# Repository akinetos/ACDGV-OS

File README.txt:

Arduino - 1.8.15
ESP8266 Boards - 2.5.0

if (interface.anyProgramActive) {
    if (interface.showMenu) {
        if (> 2 seconds after activating or deactivating a program) {
            interface.showMenu = false;
        }
    }
}

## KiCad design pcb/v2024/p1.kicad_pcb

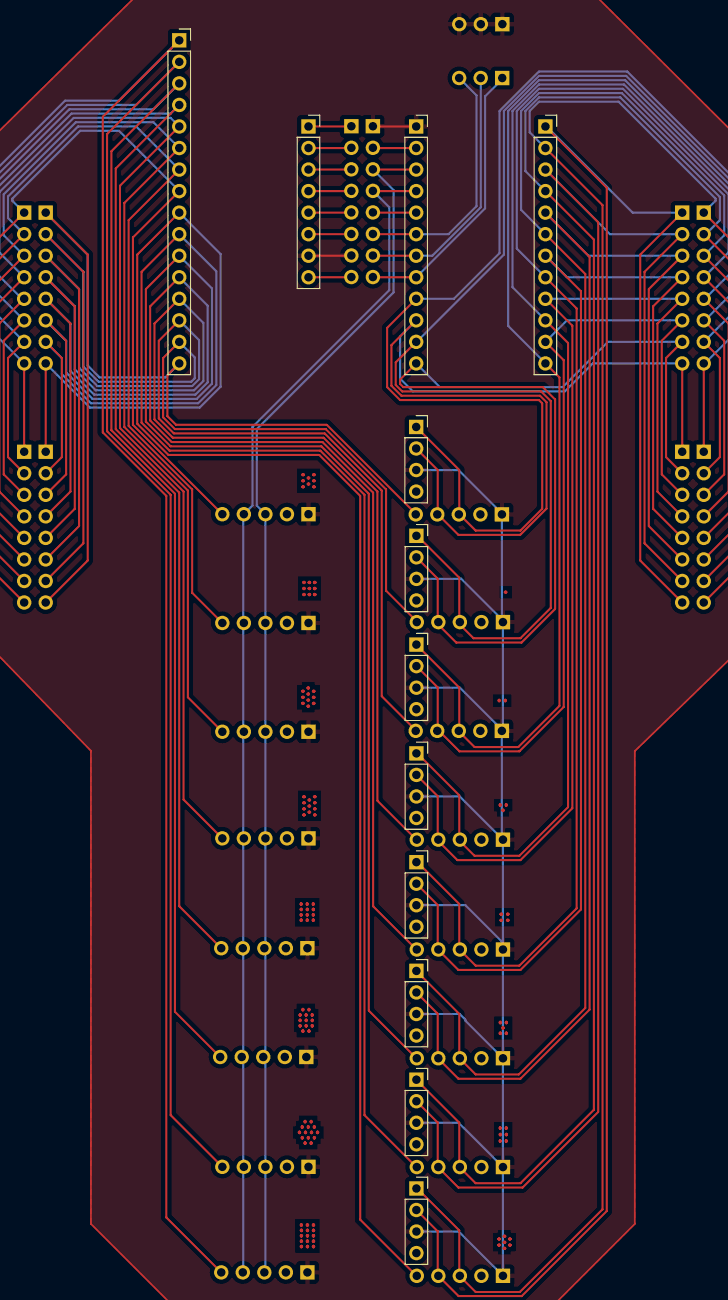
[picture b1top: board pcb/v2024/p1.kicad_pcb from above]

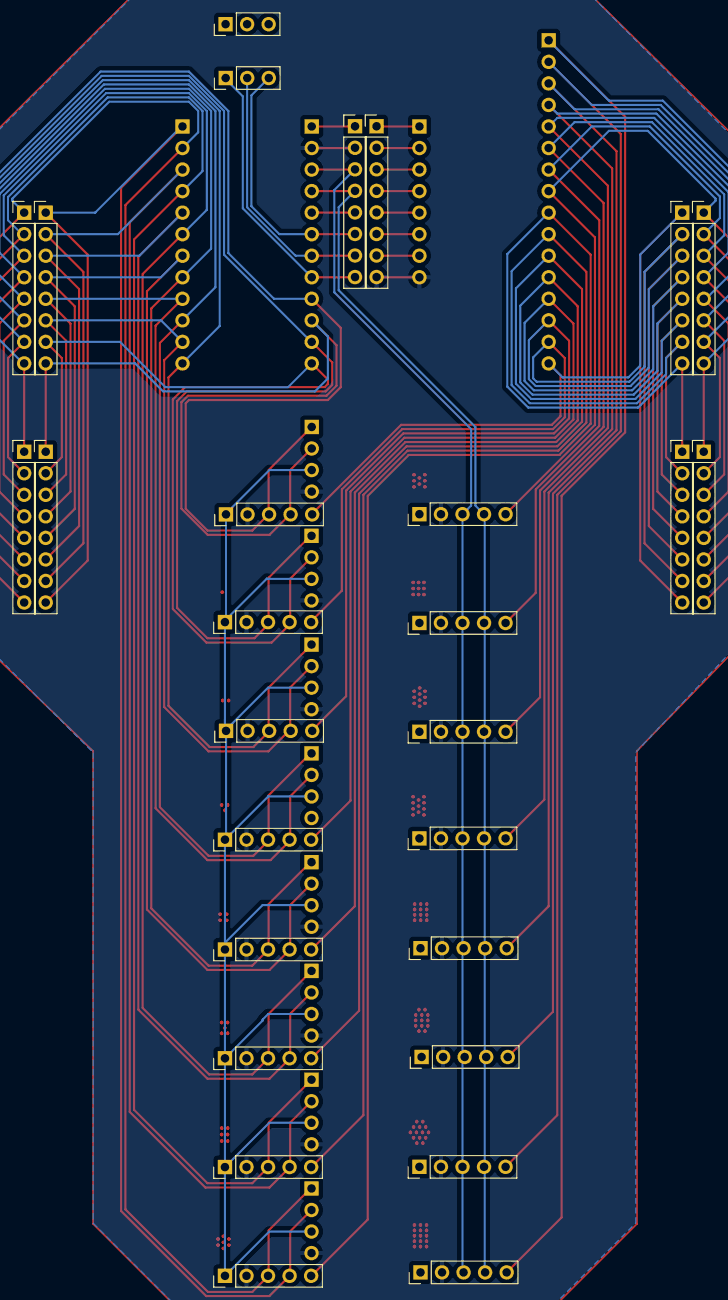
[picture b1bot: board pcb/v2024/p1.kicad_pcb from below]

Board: 2 copper layers, 40 parts (28 on the bottom side), 2 nets.

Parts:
3PIN1, 3PIN2: PinHeader_1x03_P2.54mm_Vertical
AnalogL1, AnalogL2, AnalogL3, AnalogL4: PinHeader_1x08_P2.54mm_Vertical
AnalogM1: PinSocket_1x08_P2.54mm_Vertical
AnalogM2: PinSocket_1x16_P2.54mm_Vertical
Glowne1, Glowne2: PinHeader_1x08_P2.54mm_Vertical
I2C1, I2C2, I2C3, I2C4: PinHeader_1x08_P2.54mm_Vertical
J8, J9, J10, J11, J12, J13, J14, J15: PinSocket_1x04_P2.54mm_Vertical
J16, J17, J18, J19, J20, J21, J22, J23, J24, J25, J26, J27, J28, J29, J30, J31: PinHeader_1x05_P2.54mm_Vertical
Multiplekser_I2C1, Multiplekser_I2C2: PinSocket_1x12_P2.54mm_Vertical

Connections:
GND: AnalogM1.8, Glowne1.8, Glowne2.2, J8.4, J9.4, J10.4, J12.4, J13.4, J14.4, J15.4, J16.4, J17.4, J18.4, J19.4, J20.4, J21.4, J22.4, J23.4, J24.4, J25.4, J26.4, J27.4, J28.4, J29.4, J30.4, J31.4, Multiplekser_I2C1.2
V: 3PIN1.1, 3PIN1.2, 3PIN1.3, AnalogM1.7, Glowne1.7, Glowne2.1, J8.3, J9.3, J10.3, J11.3, J12.3, J13.3, J14.3, J15.3, J16.5, J17.5, J18.5, J19.5, J20.5, J21.5, J22.5, J23.5, J24.5, J25.5, J26.5, J27.5, J28.5, J29.5, J30.5, J31.5, Multiplekser_I2C1.1

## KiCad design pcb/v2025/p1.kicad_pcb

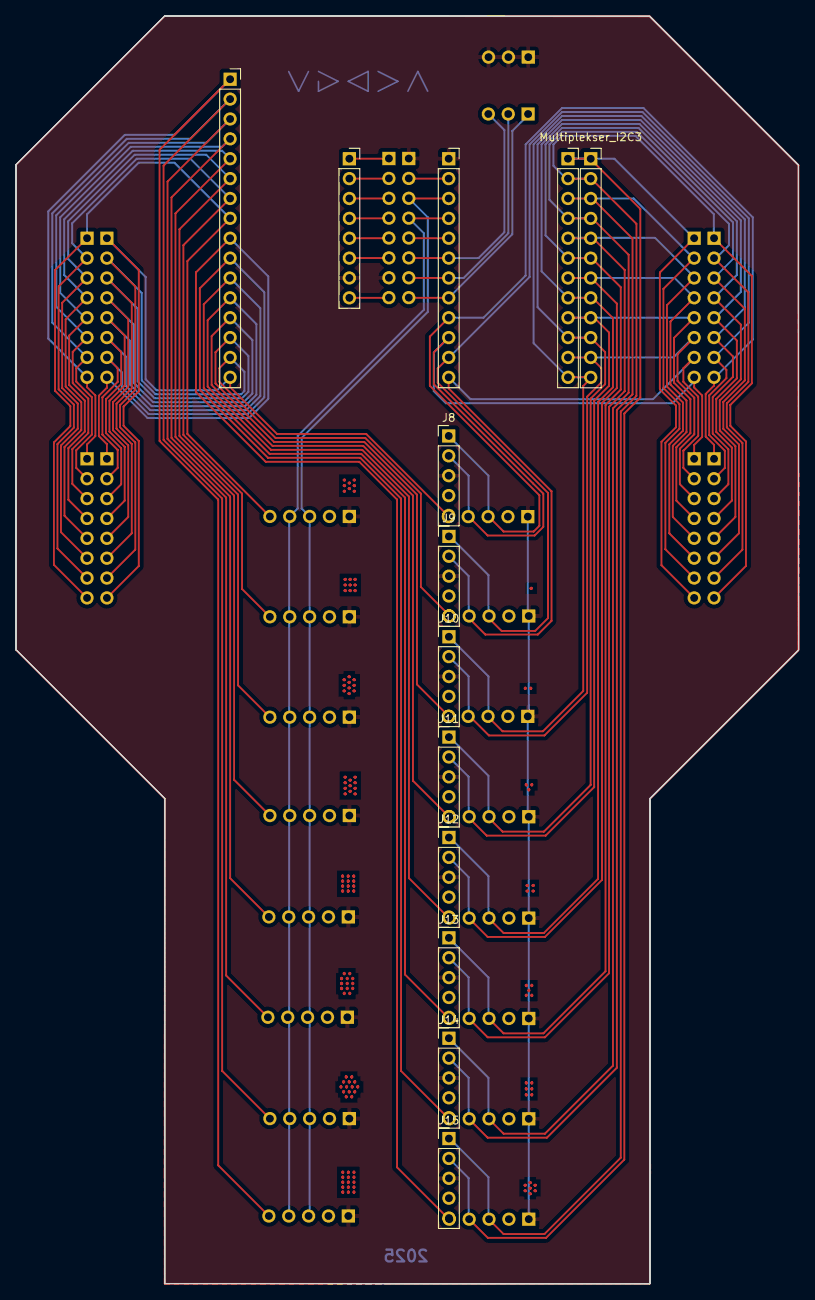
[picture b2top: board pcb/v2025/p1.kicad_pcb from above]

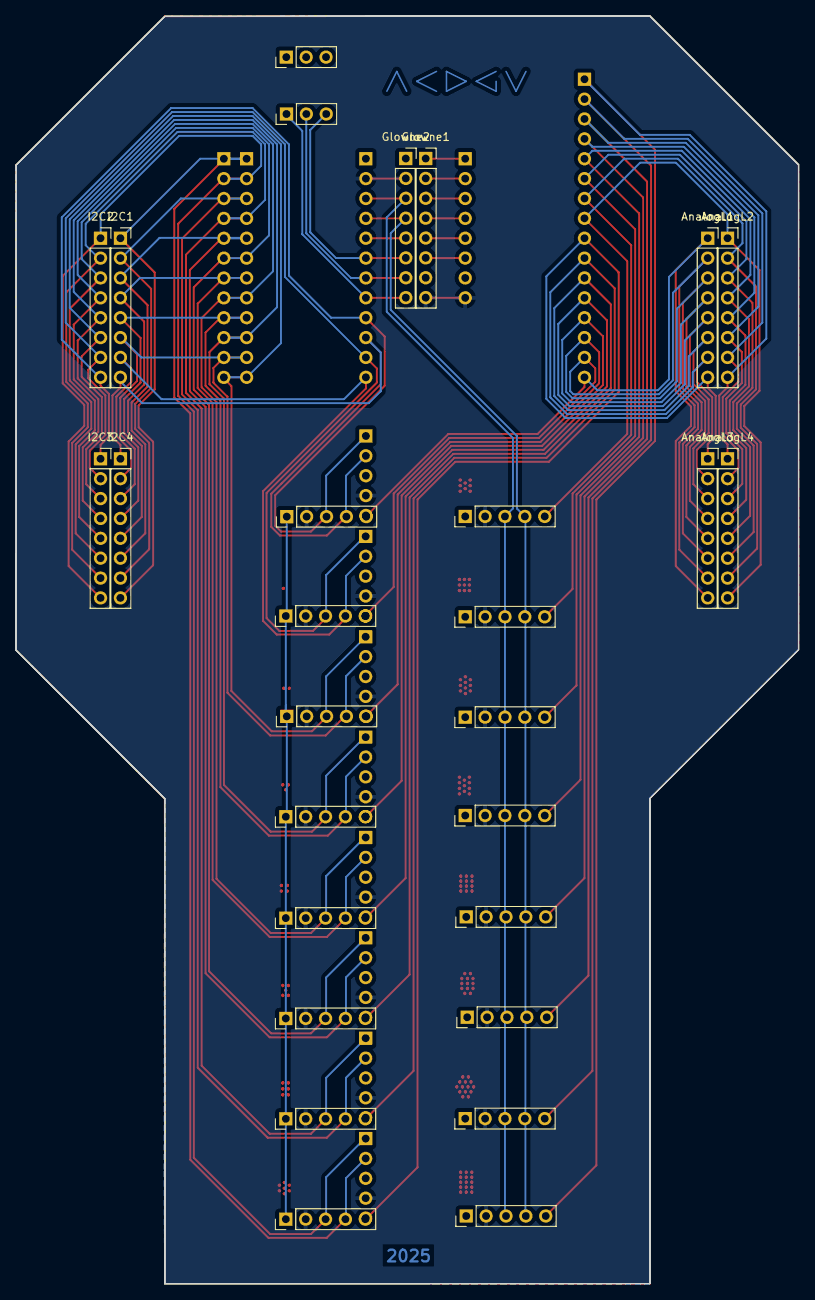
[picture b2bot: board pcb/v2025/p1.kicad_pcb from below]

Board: 2 copper layers, 100.0 x 162.1 mm, 41 parts (28 on the bottom side), 46 nets.

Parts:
3PIN1, 3PIN2: Conn_01x03; PinHeader_1x03_P2.54mm_Vertical
AnalogL1, AnalogL2, AnalogL3, AnalogL4: Conn_01x08_Pin; PinSocket_1x08_P2.54mm_Vertical
AnalogM1: Conn_01x08_Pin; PinSocket_1x08_P2.54mm_Vertical
AnalogM2: Conn_01x16_Pin; PinSocket_1x16_P2.54mm_Vertical
Glowne1, Glowne2: Conn_01x08_Pin; PinSocket_1x08_P2.54mm_Vertical
I2C1, I2C2, I2C3, I2C4: Conn_01x08_Pin; PinSocket_1x08_P2.54mm_Vertical
J8, J9, J10, J11, J12, J13, J14, J15: Conn_01x04; PinHeader_1x05_P2.54mm_Vertical
J16, J17, J18, J19, J20, J21, J22, J23, J24, J25, J26, J27, J28, J29, J30, J31: Conn_01x05; PinHeader_1x05_P2.54mm_Vertical
Multiplekser_I2C1, Multiplekser_I2C2, Multiplekser_I2C3: Conn_01x12_Pin; PinSocket_1x12_P2.54mm_Vertical

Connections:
A0: AnalogL1.1, AnalogL3.8, AnalogM2.16, J16.1
A1: AnalogL1.2, AnalogL3.7, AnalogM2.15, J17.1
A2: AnalogL1.3, AnalogL3.6, AnalogM2.14, J18.1
A3: AnalogL1.4, AnalogL3.5, AnalogM2.13, J19.1
A4: AnalogL1.5, AnalogL3.4, AnalogM2.12, J20.1
A5: AnalogL1.6, AnalogL3.3, AnalogM2.11, J21.1
A6: AnalogL1.7, AnalogL3.2, AnalogM2.10, J22.1
A7: AnalogL1.8, AnalogL3.1, AnalogM2.9, J23.1
A8: AnalogL2.1, AnalogL4.8, AnalogM2.8, J24.1
A9: AnalogL2.2, AnalogL4.7, AnalogM2.7, J25.1
A10: AnalogL2.3, AnalogL4.6, AnalogM2.6, J26.1
A11: AnalogL2.4, AnalogL4.5, AnalogM2.5, J27.1
A12: AnalogL2.5, AnalogL4.4, AnalogM2.4, J28.1
A13: AnalogL2.6, AnalogL4.3, AnalogM2.3, J29.1
A14: AnalogL2.7, AnalogL4.2, AnalogM2.2, J30.1
A15: AnalogL2.8, AnalogL4.1, AnalogM2.1, J31.1
EN: AnalogM1.6, Glowne1.6
GND: AnalogM1.8, Glowne1.8, Glowne2.2, J8.4, J9.4, J10.4, J11.4, J12.4, J13.4, J14.4, J15.4, J16.4, J17.4, J18.4, J19.4, J20.4, J21.4, J22.4, J23.4, J24.4, J25.4, J26.4, J27.4, J28.4, J29.4, J30.4, J31.4, Multiplekser_I2C1.2
IA0: 3PIN2.1, Glowne2.6, Multiplekser_I2C1.6
IA1: 3PIN2.2, Glowne2.7, Multiplekser_I2C1.7
IA2: 3PIN2.3, Glowne2.8, Multiplekser_I2C1.8
RST: Glowne2.5, Multiplekser_I2C1.5
S0: AnalogM1.5, Glowne1.5
S1: AnalogM1.4, Glowne1.4
S2: AnalogM1.3, Glowne1.3
S3: AnalogM1.2, Glowne1.2
SC0: I2C1.8, I2C4.1, J8.2, J16.2, Multiplekser_I2C1.10
SC1: I2C1.7, I2C4.2, J9.2, J17.2, Multiplekser_I2C1.12
SC2: I2C1.6, I2C4.3, J10.2, J18.2, Multiplekser_I2C2.11, Multiplekser_I2C3.11
SC3: I2C1.5, I2C2.5, I2C4.4, J11.2, J19.2, Multiplekser_I2C2.9, Multiplekser_I2C3.9
SC4: I2C1.4, I2C4.5, J12.2, J20.2, Multiplekser_I2C2.7, Multiplekser_I2C3.7
SC5: I2C1.3, I2C4.6, J13.2, J21.2, Multiplekser_I2C2.5, Multiplekser_I2C3.5
SC6: I2C1.2, I2C4.7, J14.2, J22.2, Multiplekser_I2C2.3, Multiplekser_I2C3.3
SC7: I2C1.1, I2C4.8, J15.2, J23.2, Multiplekser_I2C2.1, Multiplekser_I2C3.1
SCL: Glowne2.4, J24.2, J25.2, J26.2, J27.2, J28.2, J29.2, J30.2, J31.2, Multiplekser_I2C1.4
SD0: I2C2.8, I2C3.1, J8.1, J16.3, Multiplekser_I2C1.9
SD1: I2C2.7, I2C3.2, J9.1, J17.3, Multiplekser_I2C1.11
SD2: I2C2.6, I2C3.3, J10.1, J18.3, Multiplekser_I2C2.12, Multiplekser_I2C3.12
SD3: I2C3.4, J11.1, J19.3, Multiplekser_I2C2.10, Multiplekser_I2C3.10
SD4: I2C2.4, I2C3.5, J12.1, J20.3, Multiplekser_I2C2.8, Multiplekser_I2C3.8
SD5: I2C2.3, I2C3.6, J13.1, J21.3, Multiplekser_I2C2.6, Multiplekser_I2C3.6
SD6: I2C2.2, I2C3.7, J14.1, J22.3, Multiplekser_I2C2.4, Multiplekser_I2C3.4
SD7: I2C2.1, I2C3.8, J15.1, J23.3, Multiplekser_I2C2.2, Multiplekser_I2C3.2
SDA: Glowne2.3, J24.3, J25.3, J26.3, J27.3, J28.3, J29.3, J30.3, J31.3, Multiplekser_I2C1.3
SIG: AnalogM1.1, Glowne1.1
V: 3PIN1.1, 3PIN1.2, 3PIN1.3, AnalogM1.7, Glowne1.7, Glowne2.1, J8.3, J9.3, J10.3, J11.3, J12.3, J13.3, J14.3, J15.3, J16.5, J17.5, J18.5, J19.5, J20.5, J21.5, J22.5, J23.5, J24.5, J25.5, J26.5, J27.5, J28.5, J29.5, J30.5, J31.5, Multiplekser_I2C1.1

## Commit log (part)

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2025-07-23 Analog Clock Digital Ground Voltage - Operating System
2025-07-24 IMP: batterfly, menu
2025-07-24 ADD: keypad
2025-07-25 IMP: batterfly
2025-07-25 FIX: batterfly
2025-07-25 FIX: back button
2025-07-26 IMP: programs management
2025-07-26 IMP: interface
2025-07-27 ADD: interface hover effect
2025-07-27 FIX: gravity
2025-07-27 FIX: keypad
2025-07-27 IMP: tiding up imports
2025-07-28 IMP: telephone
2025-07-28 ADD: connecting to WiFi
2025-07-30 testing websocket
2025-07-30 IMP: WiFi
2025-07-31 IMP: interface menu path
2025-08-01 FIX: preview surface
2025-08-01 ADD: fading out path when program opened
2025-08-01 IMP: shortening
2025-08-02 IMP: tiding up
2025-08-02 IMP: interface code readability
2025-08-03 tiding up
2025-08-03 IMP: handling main menu
2025-08-03 IMP: main menu
2025-08-04 ADD: using keypad to select options
2025-08-04 ADD: using keypad to navigate the main menu
2025-08-05 ADD: multitasking
2025-08-06 IMP: multitasking
2025-08-06 IMP: multitasking and VV
2025-08-07 IMP: tiding up program class
2025-08-11 IMP: sensors as array of devices of ports
2025-08-12 FIX: surface 8x1
2025-08-15 ADD: communicating over i2c
2025-08-16 ADD: HTTP server
2025-08-17 ADD: serves as backwoods of mindifier
2025-08-18 IMP: websocket
2025-08-20 ADD: adapter for only one channel with one surface
2025-08-21 ADD: programs to menu
2025-08-22 ADD: i2c scanner
2025-08-22 ADD: i2c scanner - detecting known devices
2025-08-23 ADD: data/config/devices.json
2025-08-27 ADD: loading surfaces configuration from a file
2025-08-27 ADD: dynamically loading configuration of surfaces and devices from files
2025-08-27 ADD: surfaces configuration for one surface with 8 screens
2025-08-27 ADD: storage helper
2025-08-27 IMP: automatically calculating value of channelsCount
2025-08-28 ADD: detecting number of channels automatically
2025-08-28 IMP: tiding up automatic detection of channelsCount
2025-08-29 IMP: detecting number of screens automatically - started
2025-08-31 FIX: loading config
2025-08-31 ADD: detecting number of screens automatically - in progress
2025-09-03 FIX: accelerometer
2025-09-04 FIX: screens refresh performance
2025-09-05 FIX: i2c and VV programs
2025-09-07 FIX: interface
2025-09-08 IMP: tiding up counting screens
2025-09-08 FIX: accelerometer orientation
2025-09-09 FIX: switching between programs
2025-09-11 FIX: logo and telephone programs, tiding up main menu
2025-09-12 IMP: tiding up interface
2025-09-13 tiding up menu
2025-09-13 IMP: gravity program
2025-09-13 IMP: gravity
2025-09-13 IMP: VV
2025-09-14 IMP: batterfly ending splash screen
2025-09-14 FIX: freezing pointer on the right side
2025-09-15 IMP: updating programs before surface gets cleared so it knows which screens need refreshing
2025-09-15 IMP: VV - moved data-related tasks to update() and left only drawing in tick()
2025-09-17 FIX: VV and gravity
2025-09-19 FIX: VV freezing on exitting
2025-09-20 ADD: running multiple programs at once
2025-09-27 ADD: one option per screen if 8 screens available
2025-09-30 IMP: keeping state of the main menu
2025-10-01 IMP: tiding up interfafce menu
2025-10-01 ADD: counting of options starts from 1, not 0
2025-10-01 IMP: data structure of menu.json
2025-10-01 ADD: dzieci program
2025-10-02 FIX: refreshing all screens after selecting menu option
2025-10-03 FIX: clearing screens when changing menu path
2025-10-05 ADD: gesture detector
2025-10-07 IMP: accelerometer orientation
2025-10-07 FIX: flickering when selecting option from the menu
2025-10-10 FIX: stability
2025-10-10 ADD: program dzieci
2025-10-12 ADD: gesture detector in gravity
2025-10-12 FIX: gesture detector on gravity
2025-10-12 FIX: VV leftovers
2025-10-12 IMP: logo
2025-10-17 dodałem obsługę NFC ale narazie w głównym pliku wejściowym, trzeba przenieść do devices/NFC.h
2025-10-17 rzeczy odpowiedzialne za NFC przeniesione do programs/NFC
2025-10-17 poprawki do NFC
2025-10-17 guzik x po prawej zamiast < po lewej
2025-10-19 wyświetlanie menu jako lista (index + nazwa)
2025-10-19 naprawiony kursor w okolicach scrollbara
2025-10-22 kod związany z NFC przeniesiony do devices/NFC
2025-10-22 przeniesienie rzeczy związanych z NFC fo devices/NFC
2025-10-24 zmiany w menu i urządzeniach
2025-10-24 poprawki w NFC
2025-10-24 naprawione menu w programach
2025-10-24 sprzątanie urządzeń w głównym pliku
2025-10-25 sprzątanie w interface i surface
2025-10-25 naprawione uruchamianie programów z poziomu menu głównego
2025-10-31 poprawki związane z orientacją i zapisywaniem na NFC
2025-11-02 engine powinien ładować się przed wszystkim innym
2025-11-02 sprzątanie importów w głównym pliku
2025-11-02 poprawianie kolejności importów w głównym pliku
2025-11-03 porządkowanie importów
2025-11-08 próba wyeliminowania odwołań do gamepad w pliku inteerface
2025-11-09 sprzątanie importów w głownym pliku
2025-11-09 sprzątanie w urządzeniach
2025-11-09 sprzątanie w surface.drawMenuOptions
2025-11-09 zapisywanie współrzędnych w VV na NFC
2025-11-11 naprawiony problem z liniami w VV, informowanie o zapisaniu na NFC w VV
2025-11-11 program do obsługi baterii
2025-11-14 poprawki do programu i2c
2025-11-14 pliki związane z płytką pcb
2025-11-18 poprawki w programie i2c
2025-11-18 naprawiony program i2c
2025-11-20 sprzątanie funkcji loop w głównym pliku
2025-11-23 sprzątanie funcji tick w głównym pliku
2025-11-29 sprzątanie w płaszczyznach
2025-11-30 dodałem klasę storage do obsługi czytania danych z plików
2025-12-17 sprzątanie w importach
2025-12-18 podświetlanie wiersza pod kursorem
2025-12-18 channel.display() moved to surface.display()
2025-12-18 sprzątanie w tworzeniu płaszczyzn
2025-12-21 poprawka do obsługi kierunku kursora
2025-12-21 gamepad guzik - obsługa krótkiego naciśnięcia i długiego
2025-12-22 naprawione pokazywanie obrazu w VV
2025-12-22 VV - blokowanie kursora w trakcie ruszania tłem
2025-12-23 poprawka do orientacji w osi X w klasie surface
2025-12-24 sprzątanie głównej funkcji loop
2025-12-24 VV - chowanie menu i kursora przy ruszaniu tłem
2025-12-26 sprzątanie w głównej funkcji loop
2025-12-26 zmiana nazwy Interface -> Menu
2025-12-27 sprzątanie w funkcji loop
2025-12-28 poprawka do programu grawitacja
2025-12-29 sprzątanie w głównej funkcji setup
2025-12-29 sprzątanie w funkcji setup
2025-12-29 program w tle i jednoczesne wykonywanie wielu programów
2025-12-30 sprzątanie w zarządzaniu płaszczyznami
2025-12-30 pozycjonowanie tła
2026-01-02 poprawka w menu
2026-01-03 menu główne - dodane ustawienia
2026-01-05 animacja kursora po wciśnięciu guzika
2026-01-05 sprzątanie w gamepad - axisX -> x, axisY -> y
2026-01-08 sprzątanie obsługi gamepada
2026-01-10 zarządzanie aktywnymi programami
2026-01-16 naprawiona obsługa NFC w VV
2026-01-19 integracja urządzenia keypad z menu
2026-01-20 nawigacja po menu za pomocą keypad - zamykanie za pomocą *
2026-01-28 pokrowiec
2026-01-28 sprzątanie w plikach pod kątem wifi
2026-01-30 gamepad i akcelerometr przez websocket
2026-02-01 naprawienie łączności przez wifi
2026-02-01 poprawiona detekcja zmian w gemepad i akcelerometrze
2026-02-01 wizualizacja gamepada i akcelerometru
2026-02-02 poprawki w wizualizacji gamepada i akcelerometru przez websocket
2026-02-06 nfc przez wifi
2026-02-06 czytanie tagu nfc i wysyłanie przez websocket
2026-02-08 usprawnienie detekcji zmian w nfc
2026-02-08 zapis na NFC
2026-02-09 sprzątanie w zdalnej obsłudze nfc
2026-02-11 poprawki w interfejsie www
2026-02-18 testing wifi with different router
2026-02-21 poprawki sieciowe
2026-02-23 integracja z Mindifier
2026-02-25 zaktualizowane pliki z mindifiera
2026-02-27 pcb v2024, v2025
2026-03-05 poprawki w zdalnym interfejsie
2026-03-28 poprawka w programie gravity
2026-03-30 loading coordinates from nfc in VV
2026-04-24 ulepszenia architektoniczne
2026-04-25 usprawnione uruchamianie programów
2026-04-26 sprzątanie w menu i oled
2026-05-01 naprawiony kierunek wskaznika
2026-05-01 poprawki w menu i motylu
2026-05-17 przewijanie obrazków w kontaktach
2026-05-19 dodane opcje do programu kontakty
2026-05-20 poprawka do wykonywania programów z menu głównego
2026-05-20 naprawiona lista kamer
2026-05-20 poprawiona obsługa menu
2026-05-21 sprzątanie w programach
2026-05-22 przejścia - praca w toku
2026-05-23 przejscia - prawe gotowe
2026-05-24 przejścia - sprzątanie
2026-05-24 przejscia - sprzątanie
2026-05-24 przeniosłem funkcję execute(command) z menu do głównego pliku
2026-05-24 effects => transitions
2026-05-29 przejścia między programami
2026-05-29 zarządzanie programami - sprzątanie
2026-05-30 ulepszenia w sterowaniu menu i w przejściach
2026-05-31 spadające piksele przy zamykaniu programu :)
2026-06-01 naprawiona nawigacja w VV
2026-06-04 zapamiętywanie poziomu menu aktywnego programu
2026-06-04 sprzątane w przejściach
2026-06-04 sprzątanie w pliku głównym
2026-06-04 sprzątanie pliku głównego
2026-06-07 sprzątanie w prejściach
2026-06-09 przejścia między elementami menu
2026-06-13 poprawiona obsługa przejść
2026-06-14 poprawienie obsługi menu
2026-06-18 przeniosłem rysowanie menu do z surface.h do menu.h
2026-06-18 przeniosłem kod związany z menu z surface.h do menu.h
2026-06-18 sprzątanie w menu
2026-06-18 ulepszenie menu
2026-06-23 uproszczenie obsługi sensorów
